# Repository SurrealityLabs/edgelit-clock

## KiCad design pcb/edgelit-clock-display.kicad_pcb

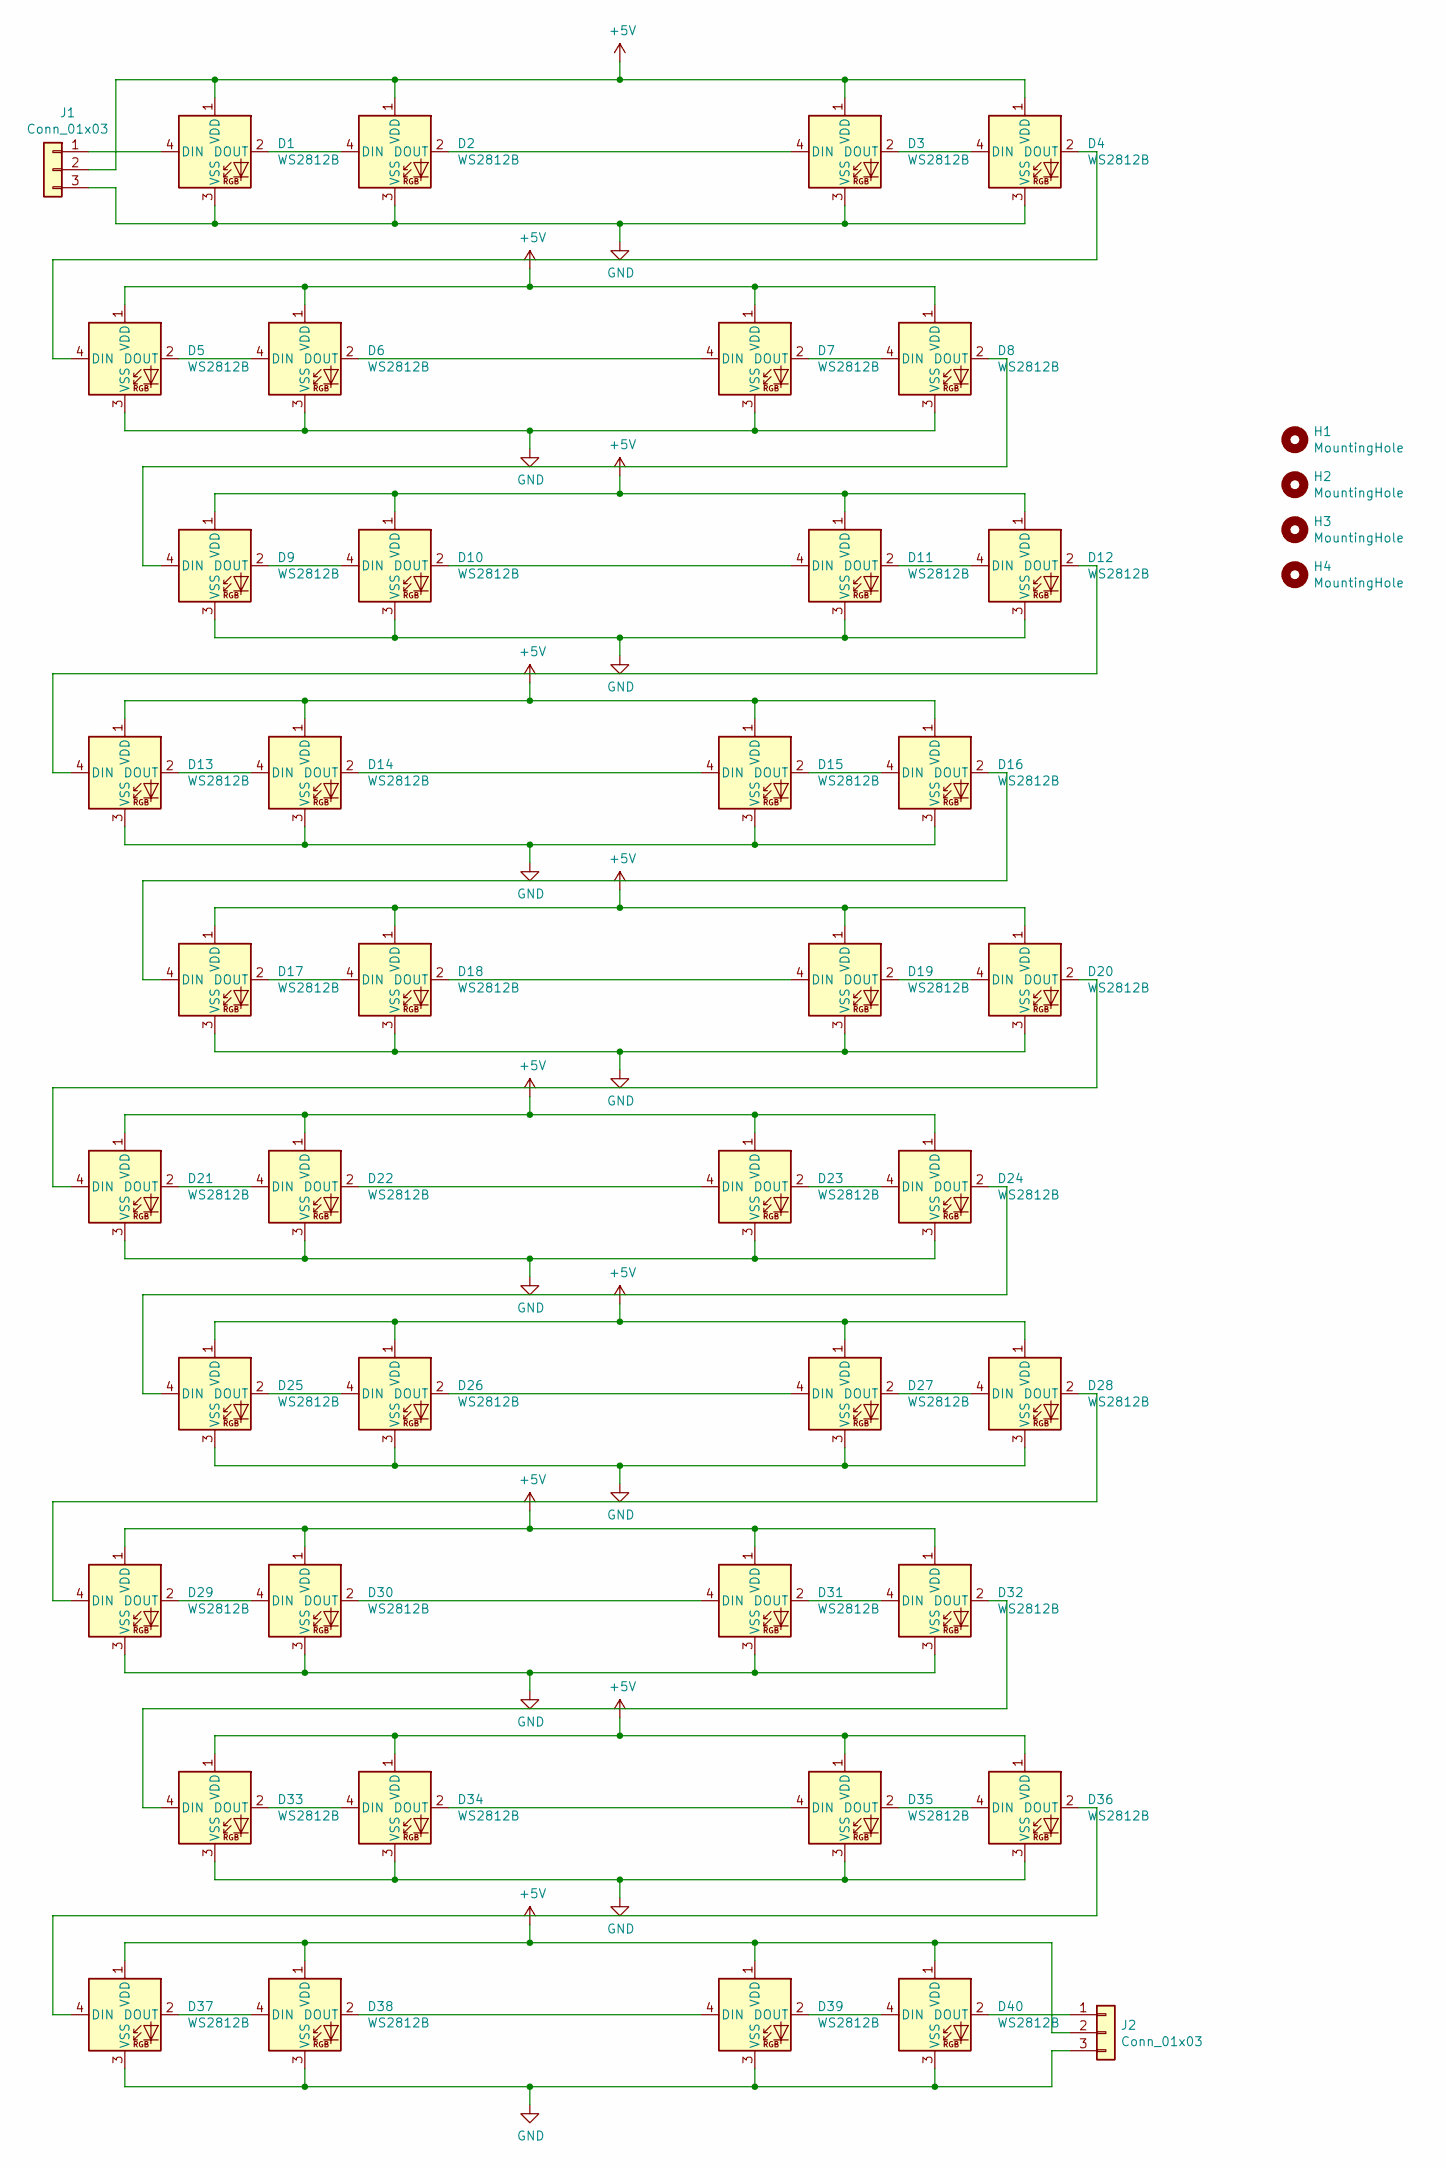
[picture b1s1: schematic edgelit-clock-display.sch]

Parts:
D1, D2, D3, D4, D5, D6, D7, D8, D9, D10, D11, D12, D13, D14, D15, D16, D17, D18, D19, D20, D21, D22, D23, D24, D25, D26, D27, D28, D29, D30, D31, D32, D33, D34, D35, D36, D37, D38, D39, D40: WS2812B; WS2812-2020; LCSC C965555
H1, H2, H3, H4: MountingHole; MountingHole_3.2mm_M3_DIN965
J1, J2: Conn_01x03; JST_PH_S3B-PH-SM4-TB_1x03-1MP_P2.00mm_Horizontal

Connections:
+5V: D1.1 (VDD), D2.1 (VDD), D3.1 (VDD), D4.1 (VDD), D5.1 (VDD), D6.1 (VDD), D7.1 (VDD), D8.1 (VDD), D9.1 (VDD), D10.1 (VDD), D11.1 (VDD), D12.1 (VDD), D13.1 (VDD), D14.1 (VDD), D15.1 (VDD), D16.1 (VDD), D17.1 (VDD), D18.1 (VDD), D19.1 (VDD), D20.1 (VDD), D21.1 (VDD), D22.1 (VDD), D23.1 (VDD), D24.1 (VDD), D25.1 (VDD), D26.1 (VDD), D27.1 (VDD), D28.1 (VDD), D29.1 (VDD), D30.1 (VDD), D31.1 (VDD), D32.1 (VDD), D33.1 (VDD), D34.1 (VDD), D35.1 (VDD), D36.1 (VDD), D37.1 (VDD), D38.1 (VDD), D39.1 (VDD), D40.1 (VDD), J1.2, J2.2
GND: D1.3 (VSS), D2.3 (VSS), D3.3 (VSS), D4.3 (VSS), D5.3 (VSS), D6.3 (VSS), D7.3 (VSS), D8.3 (VSS), D9.3 (VSS), D10.3 (VSS), D11.3 (VSS), D12.3 (VSS), D13.3 (VSS), D14.3 (VSS), D15.3 (VSS), D16.3 (VSS), D17.3 (VSS), D18.3 (VSS), D19.3 (VSS), D20.3 (VSS), D21.3 (VSS), D22.3 (VSS), D23.3 (VSS), D24.3 (VSS), D25.3 (VSS), D26.3 (VSS), D27.3 (VSS), D28.3 (VSS), D29.3 (VSS), D30.3 (VSS), D31.3 (VSS), D32.3 (VSS), D33.3 (VSS), D34.3 (VSS), D35.3 (VSS), D36.3 (VSS), D37.3 (VSS), D38.3 (VSS), D39.3 (VSS), D40.3 (VSS), J1.3, J2.3
unnamed: D1.2 (DOUT), D2.4 (DIN)
unnamed: D1.4 (DIN), J1.1
unnamed: D2.2 (DOUT), D3.4 (DIN)
unnamed: D3.2 (DOUT), D4.4 (DIN)
unnamed: D4.2 (DOUT), D5.4 (DIN)
unnamed: D5.2 (DOUT), D6.4 (DIN)
unnamed: D6.2 (DOUT), D7.4 (DIN)
unnamed: D7.2 (DOUT), D8.4 (DIN)
unnamed: D8.2 (DOUT), D9.4 (DIN)
unnamed: D10.2 (DOUT), D11.4 (DIN)
unnamed: D9.2 (DOUT), D10.4 (DIN)
unnamed: D11.2 (DOUT), D12.4 (DIN)
unnamed: D12.2 (DOUT), D13.4 (DIN)
unnamed: D13.2 (DOUT), D14.4 (DIN)
unnamed: D14.2 (DOUT), D15.4 (DIN)
unnamed: D15.2 (DOUT), D16.4 (DIN)
unnamed: D16.2 (DOUT), D17.4 (DIN)
unnamed: D17.2 (DOUT), D18.4 (DIN)
unnamed: D18.2 (DOUT), D19.4 (DIN)
unnamed: D19.2 (DOUT), D20.4 (DIN)
unnamed: D20.2 (DOUT), D21.4 (DIN)
unnamed: D21.2 (DOUT), D22.4 (DIN)
unnamed: D22.2 (DOUT), D23.4 (DIN)
unnamed: D23.2 (DOUT), D24.4 (DIN)
unnamed: D24.2 (DOUT), D25.4 (DIN)
unnamed: D25.2 (DOUT), D26.4 (DIN)
unnamed: D26.2 (DOUT), D27.4 (DIN)
unnamed: D27.2 (DOUT), D28.4 (DIN)
unnamed: D28.2 (DOUT), D29.4 (DIN)
unnamed: D29.2 (DOUT), D30.4 (DIN)
unnamed: D30.2 (DOUT), D31.4 (DIN)
unnamed: D31.2 (DOUT), D32.4 (DIN)
unnamed: D32.2 (DOUT), D33.4 (DIN)
unnamed: D33.2 (DOUT), D34.4 (DIN)
unnamed: D34.2 (DOUT), D35.4 (DIN)
unnamed: D35.2 (DOUT), D36.4 (DIN)
unnamed: D36.2 (DOUT), D37.4 (DIN)
unnamed: D37.2 (DOUT), D38.4 (DIN)
unnamed: D38.2 (DOUT), D39.4 (DIN)
unnamed: D39.2 (DOUT), D40.4 (DIN)
unnamed: D40.2 (DOUT), J2.1

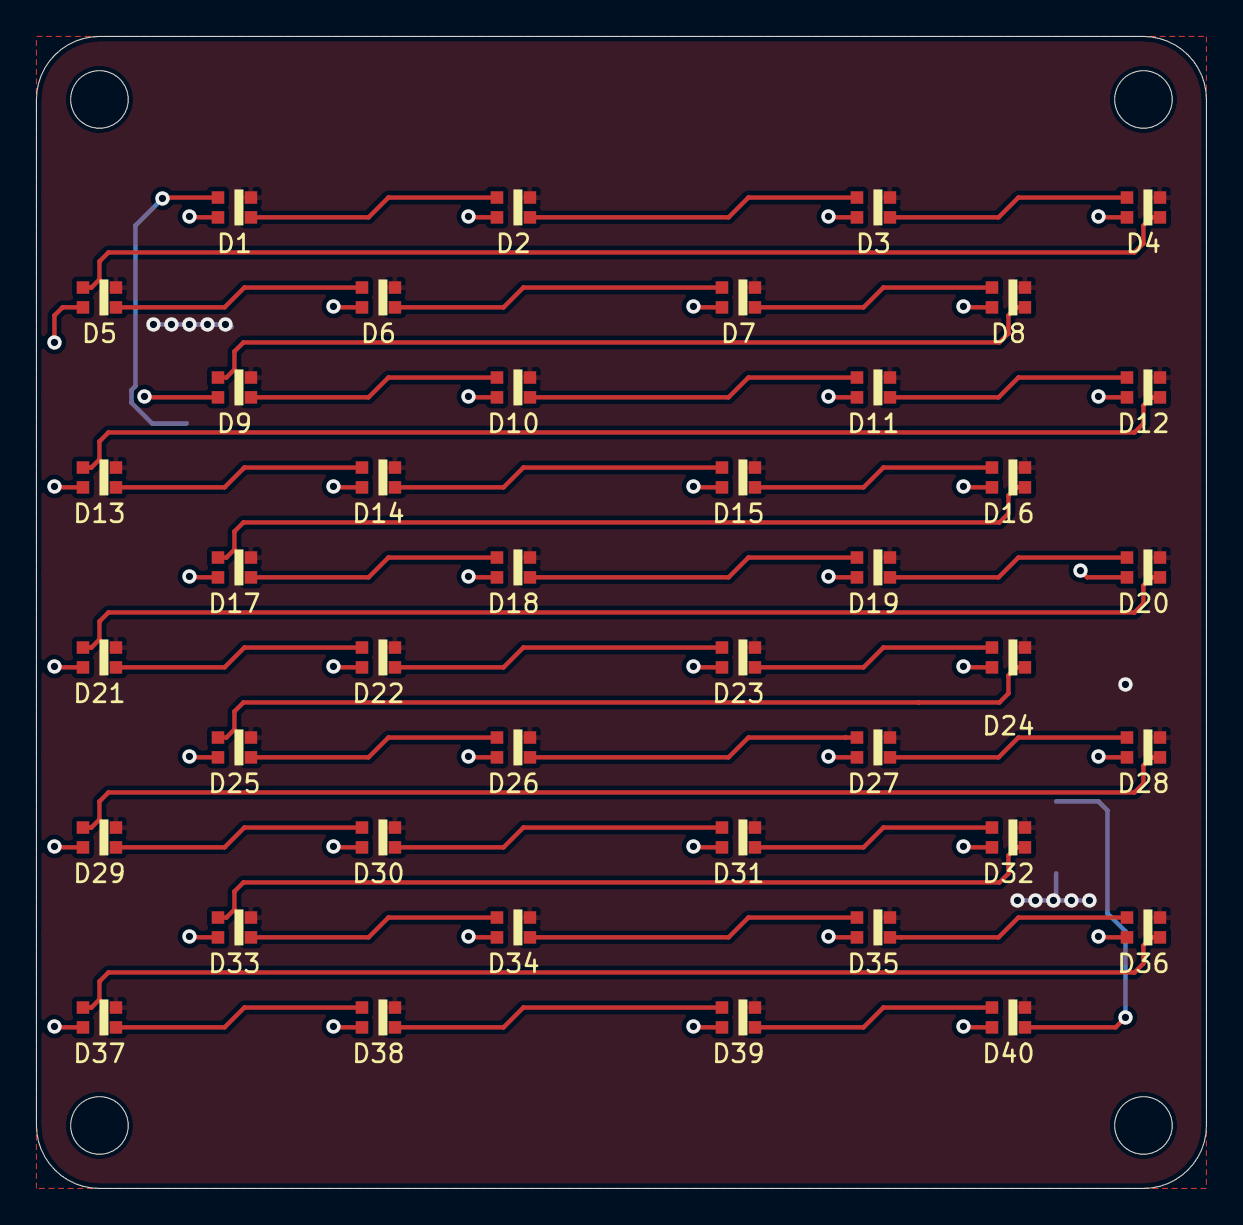
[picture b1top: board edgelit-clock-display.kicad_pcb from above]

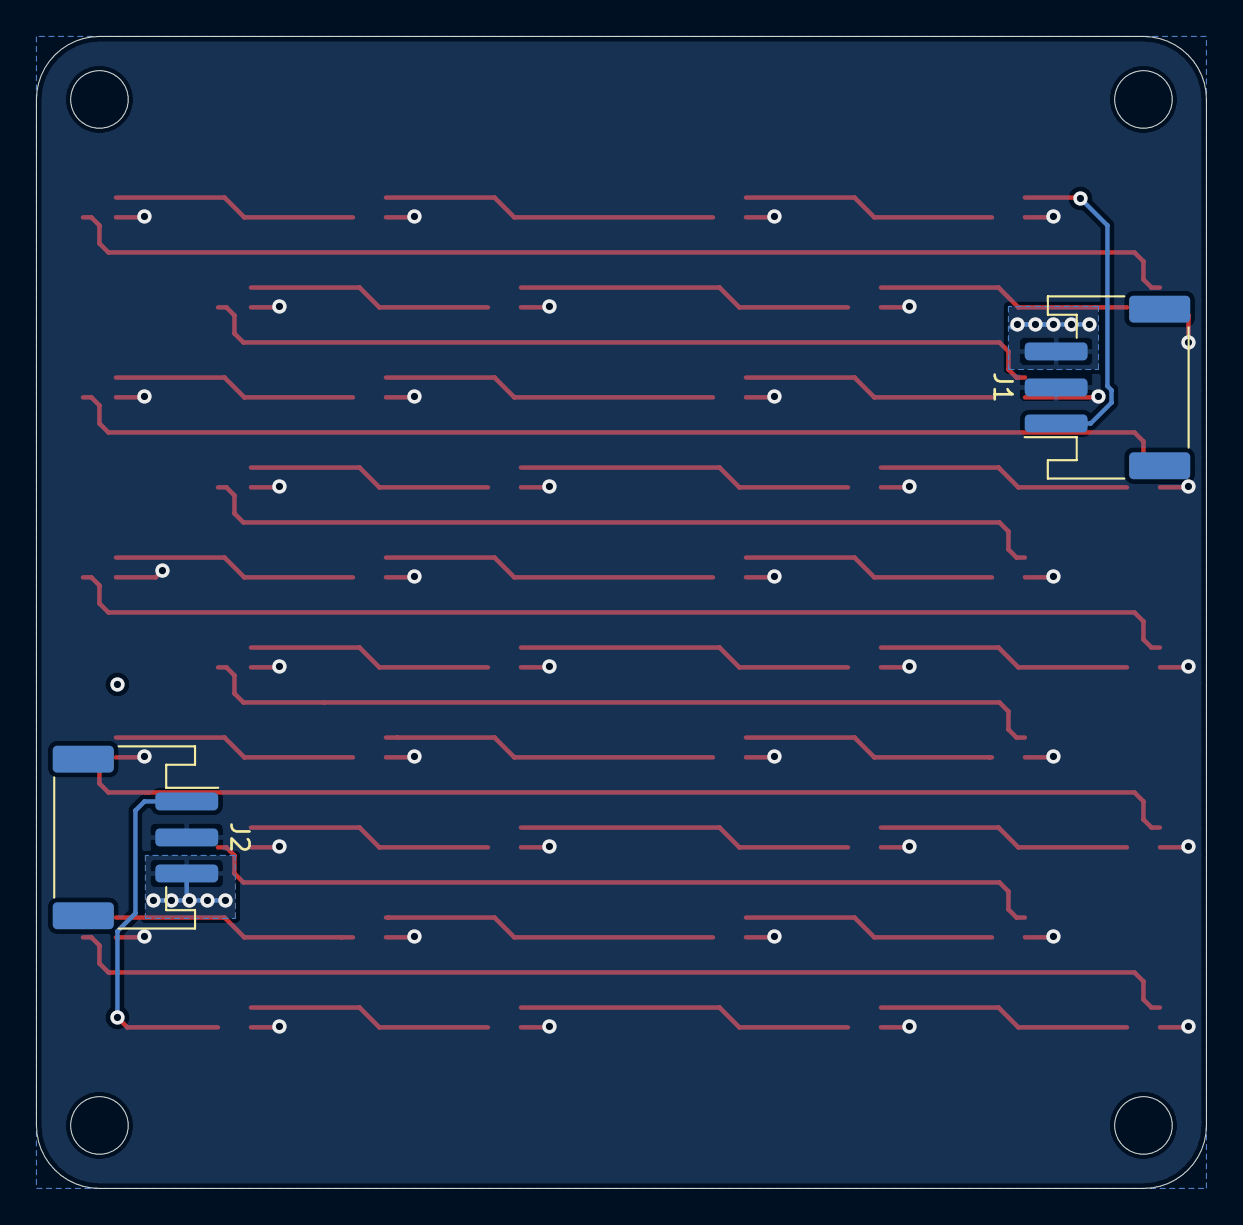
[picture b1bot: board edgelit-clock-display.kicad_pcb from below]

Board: 2 copper layers, 65.0 x 64.0 mm, 46 parts (2 on the bottom side), 43 nets.

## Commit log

2021-08-21 Adding board done with WS2812-2020 LEDs
2021-08-21 Resized for a 30mm digit width, with 5mm between digits
